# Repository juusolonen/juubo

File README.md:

# juubo ergonomic split keyboard

juubo keyboard is designed with [Ergogen](https://ergogen.cache.works/) following FlatFootFox's great guide found [here](https://flatfootfox.com/ergogen-introduction/).

## Contents

### V1

*Semi-retired V1*

V1 is a 36-key wired split keyboard, with rotary encoders on both side. It is wired with ProMicro RP2040 controllers, running with QMK. The pcb is designed so it can be made wireless with Nice!Nano controller and ZMK firmware (Firmware not provided, but V2 firmware can probably be modified eventually for V1 also). 

> `qmk` directory in this repo contains needed files to get the qmk firmware running. Note that the rotary encoders are not perfect so they might need some tweaking.
> Also note that the default keymap is a Colemak-DH with a Finnish hint.

### V2

*3D printed case for the upcoming V2*

V2 is a 40-key wireless split keyboard and it does not have the rotary encoders anymore. Designer for Nice!Nano controller. Firmware will be built with ZMK eventually.

> [ZMK module for firmware](https://github.com/juusolonen/zmk-juubo-module) is not tested yet.

### ergogen

This directory contains the ergogen files used for V1. The mountinghole.js footprint is also used in V2, though.

**The files in /external-3d-models are not my own creation. They are just added to this repo just to keep all things in the same place**

## Bill of materials

#### Both versions
| Item | Count | Note/Model |
| ----------- | ----------- | ----------- |
| Reset button | 2 |SKQGABE010 |
| Socket for MCU | 2 | 315-43-112-41-003000 Note: optional |
| Header for MCU | 2 | EBBL-112-T-E Note: optional |
| Diodes | 36/40 | 1N4148W |
| Kailh MX hotswap sockets | 36/40 |  |
| MX switches | 36/40 |  |
| MX compatible keycaps | 36/40 | Note: Couple of 3d-models for printing available |
| M2x4x3 kurled insert nuts  | 12/18 | Optional: Needed for the printable case |
| M2 laptop style screws  | 12/18 | Optional: Needed for the printable case |

### V1 only

| Item | Count | Note/Model |
| ----------- | ----------- | ----------- |
| Promicro rp2040  | 2 | |
| Resistors | 2 | ERJ-2RKF4701X Note: only for other side |
| TRRS jack | 2 | PJ-320A |
| TRRS cable | 1 |  |
| EC11 rotary encoder | 2 | E.g. EC11E18244A5 |

#### V2 only

| Item | Count | Note/Model |
| ----------- | ----------- | ----------- |
| Nice!Nano  | 2 |  |
| Power switch  | 2 | SLW-66527511-SMT-TR|
| JST connector | 2 |S2B-PH-K-S |
| Battery | 2 | Rechargeable li-ion e.g. 301230 (This should fit under the MCU) |

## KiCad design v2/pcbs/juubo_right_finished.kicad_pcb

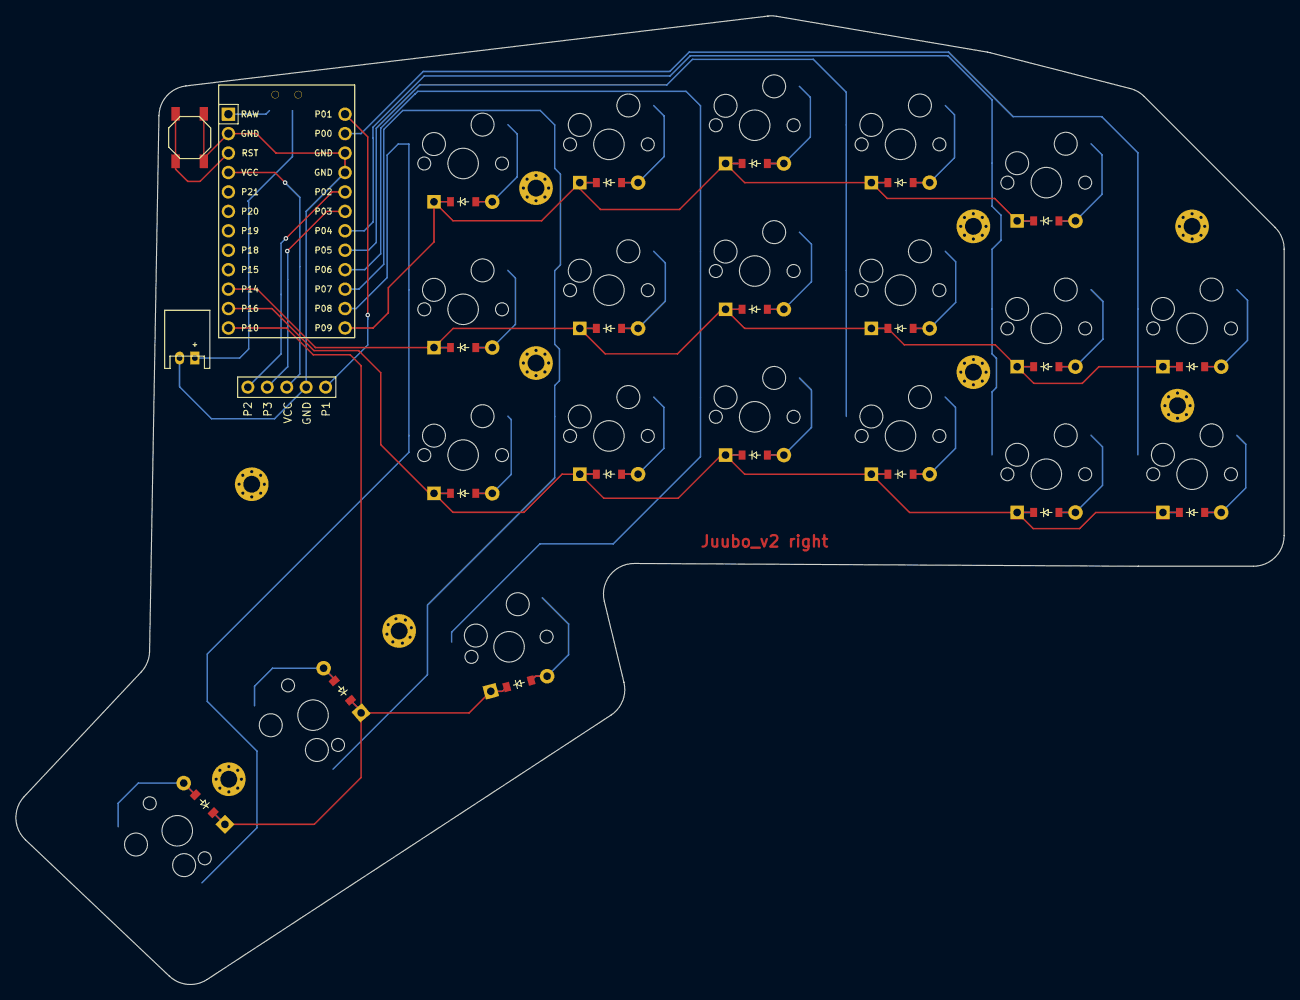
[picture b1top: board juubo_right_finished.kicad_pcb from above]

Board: 2 copper layers, 165.7 x 126.6 mm, 54 parts (0 on the bottom side), 38 nets.

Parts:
B1: SW_TACT_ALPS_SKQGABE010
D1, D2, D3, D4, D5, D6, D7, D8, D9, D10, D11, D12, D13, D14, D15, D16, D17, D18, D19, D20: ComboDiode
DISP1: display_nice_view
JST1: JST_PH_S2B-PH-K_02x2.00mm_Angled
MCU1: ProMicro
S1, S2, S3, S4, S5, S6, S7, S8, S9, S10, S11, S12, S13, S14, S15, S16, S17, S18, S19, S20: MX
T1: SPDT_C128955
_1, _2, _3, _4, _5, _6, _7, _8, _9: MountingHole_2.2mm_M2_Pad_Via

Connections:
B+: JST1.1, T1.2
GND: B1.1, DISP1.4, JST1.2, MCU1.2, MCU1.15, MCU1.16
P0: MCU1.14, S1.1, S2.1
P1: DISP1.5, MCU1.13
P2: DISP1.1, MCU1.17
P3: DISP1.2, MCU1.18
P4: MCU1.19, S3.1, S4.1, S5.1
P5: MCU1.20, S6.1, S7.1, S8.1
P6: MCU1.21, S9.1, S10.1, S11.1, S18.1
P7: MCU1.22, S12.1, S13.1, S14.1, S19.1
P8: MCU1.23, S15.1, S16.1, S17.1, S20.1
P9: D5.1, D8.1, D11.1, D14.1, D17.1, MCU1.24
P10: D18.1, D19.1, D20.1, MCU1.12
P14: D2.1, D4.1, D7.1, D10.1, D13.1, D16.1, MCU1.10
P16: D1.1, D3.1, D6.1, D9.1, D12.1, D15.1, MCU1.11
RAW: MCU1.1, T1.1
RST: B1.2, MCU1.3
VCC: DISP1.3, MCU1.4
mirror_extra_cluster: D20.2, S20.2
mirror_index_bottom: D12.2, S12.2
mirror_index_home: D13.2, S13.2
mirror_index_top: D14.2, S14.2
mirror_inner_bottom: D15.2, S15.2
mirror_inner_home: D16.2, S16.2
mirror_inner_top: D17.2, S17.2
mirror_layer_cluster: D18.2, S18.2
mirror_middle_bottom: D9.2, S9.2
mirror_middle_home: D10.2, S10.2
mirror_middle_top: D11.2, S11.2
mirror_outer_bottom: D1.2, S1.2
mirror_outer_home: D2.2, S2.2
mirror_pinky_bottom: D3.2, S3.2
mirror_pinky_home: D4.2, S4.2
mirror_pinky_top: D5.2, S5.2
mirror_ring_bottom: D6.2, S6.2
mirror_ring_home: D7.2, S7.2
mirror_ring_top: D8.2, S8.2
mirror_space_cluster: D19.2, S19.2

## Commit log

2024-01-13 Ergogen raw txt file
2024-01-13 KiCAD for left
2024-01-13 Add all ergogen files
2024-01-13 Rename kicad folder to kicad_final
2024-01-13 Add mounting holes to ergogen-generated pcb
2024-01-13 Add resistors to ergogen, add bottom case
2024-01-13 Diode pads routed
2024-01-13 Matrix traces
2024-01-14 Fix board, tweak mountingholes
2024-01-16 Ready for routing
2024-01-16 Cleanup
2024-01-17 Left routed
2024-01-18 Adjust and fix
2024-01-19 Adjust holes
2024-01-19 Switch plate things
2024-01-21 Mount plate hole adjust & opening for usb
2024-01-21 Poke hole for trrs
2024-01-21 cleaup
2024-01-21 Add right side
2024-02-02 random trash
2024-02-02 test file
2024-02-05 Add switchplate stl
2024-02-12 Add mcu cover to switch plate left
2024-02-12 poke holes to mcu cover
2024-02-13 slightly bigger holes
2024-02-21 Switchplate right done
2024-02-21 adjust mcu cover
2024-02-22 Adjust wall opening for case
2024-02-22 add external models
2024-02-23 Add models, update readme
2024-02-23 correct link
2024-03-04 adjust left case 0.5mm bigger
2024-03-05 Adjust right side to fit pcb
2024-03-05 couple of keycap models
2024-03-10 Heighten case wall & plate thickness, left side
2024-03-10 Revert plate back to 1.6mm
2024-03-11 More height
2024-03-12 Adjust right plate
2024-03-18 model
2026-01-20 Add qmk, gerber, kicad files
2026-01-21 V2 ergogen initial config, add new column, mounting points, start finetuning case and plate
2026-01-22 Adjust right side case&plate
2026-01-22 tweak nets for left half to accommodate the new column
2026-02-02 right side nets
2026-02-03 small tweak
2026-02-04 fix right
2026-02-04 remove unnecessary files
2026-02-04 remove gerbers
2026-02-04 update readme, add files
2026-02-04 images
2026-02-04 test
2026-02-05 add nice_view, move jst to side, make hole to mcu cover for display
2026-02-05 niceview to right side
2026-02-06 left side routed, add gerbers
2026-02-08 fix right side thumb columns
2026-02-08 fix right half row nets
2026-02-08 add config file changes also
2026-02-08 route right half, add gerbers
2026-02-13 readme
2026-02-14 make cases 2mm higher (for storing battery underneath pcb)
